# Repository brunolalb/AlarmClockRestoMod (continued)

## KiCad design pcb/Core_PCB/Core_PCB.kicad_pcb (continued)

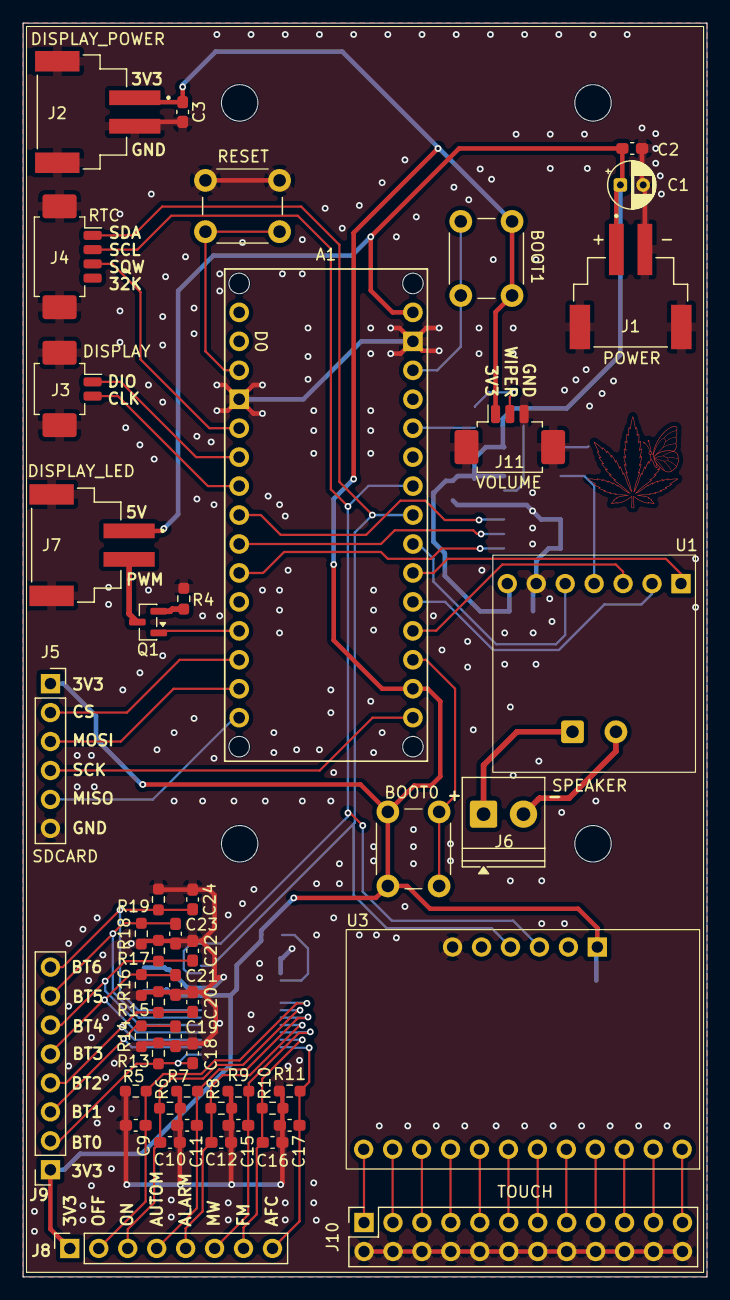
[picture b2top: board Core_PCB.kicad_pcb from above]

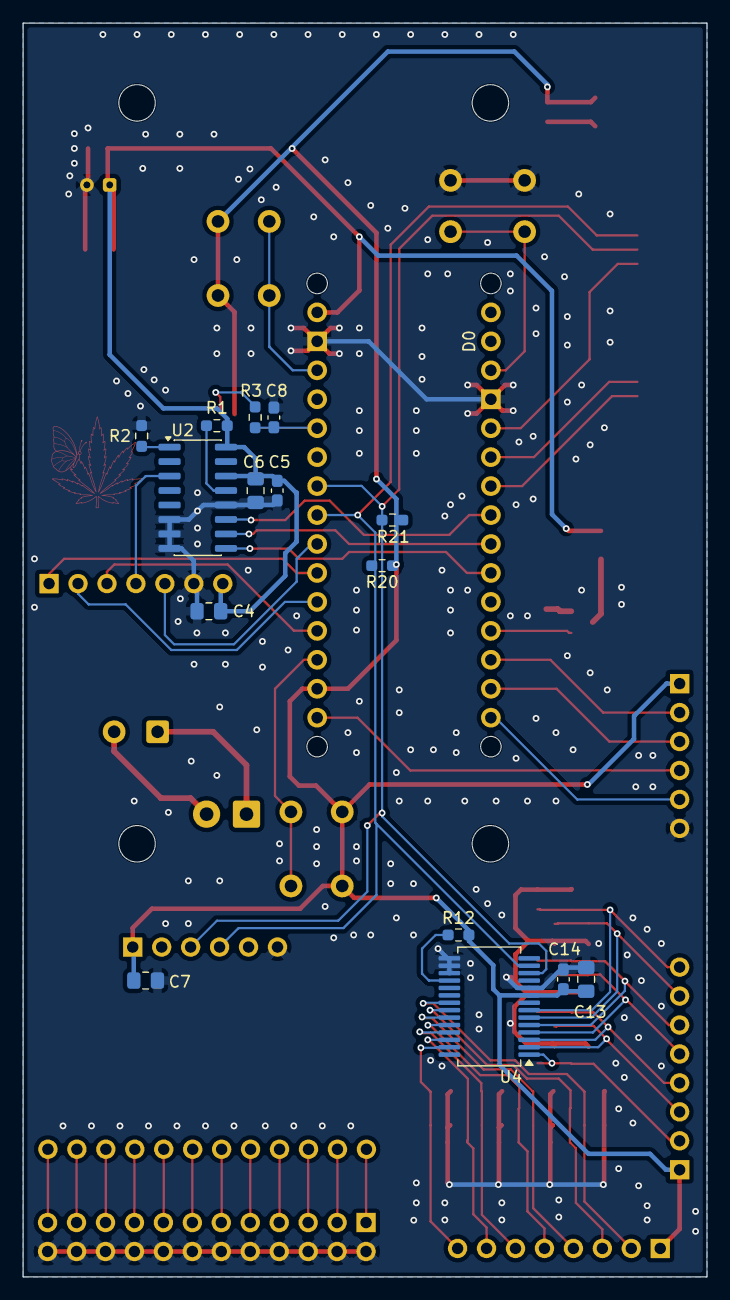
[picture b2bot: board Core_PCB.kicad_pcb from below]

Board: 2 copper layers, 60.0 x 110.0 mm, 70 parts (15 on the bottom side), 59 nets.

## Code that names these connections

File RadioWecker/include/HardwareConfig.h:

#pragma once

#include <Arduino.h>

/* Arduino Nano S3
                 ___
D13 - GPIO48 ---|   |--- D12 - GPIO47
3V3          ---|   |--- D11 - GPIO38
B0 - GPIO46  ---|   |--- D10 - GPIO21
A0 - GPIO1   ---|   |--- D9 - GPIO18
A1 - GPIO2   ---|   |--- D8 - GPIO17
A2 - GPIO3   ---|   |--- D7 - GPIO10
A3 - GPIO4   ---|   |--- D6 - GPIO9
A4 - GPIO11  ---|   |--- D5 - GPIO8
A5 - GPIO12  ---|   |--- D4 - GPIO7
A6 - GPIO13  ---|   |--- D3 - GPIO6
A7 - GPIO14  ---|   |--- D2 - GPIO5
VBUS         ---|   |--- GND
B1 - GPIO0   ---|   |--- RST
GND          ---|   |--- D0 - GPIO44
VIN          ---|___|--- D1 - GPIO43

*/

// on board LED
static constexpr uint8_t ONBOARD_LED_PIN = LED_RED;//46;

// shared I2C
static constexpr uint8_t I2C_SDA_PIN = A4;
static constexpr uint8_t I2C_SCL_PIN = A5;
static constexpr uint32_t I2C_FREQ_HZ = 100000;

// Display - TM1637
static constexpr uint8_t DISPLAY_CLK_PIN = D4;
static constexpr uint8_t DISPLAY_DIO_PIN = D3;

// todo: the TM1637 can only read one button at a time - move them to the MCP
static constexpr uint8_t DISPLAY_BUTTON_SLOW_GRID = 1;
static constexpr uint8_t DISPLAY_BUTTON_SLOW_KEY = 1;
static constexpr uint8_t DISPLAY_BUTTON_FAST_GRID = 1;
static constexpr uint8_t DISPLAY_BUTTON_FAST_KEY = 2;
static constexpr uint8_t DISPLAY_BUTTON_SLEEP_TOP_GRID = 2;
static constexpr uint8_t DISPLAY_BUTTON_SLEEP_TOP_KEY = 2;
static constexpr uint8_t DISPLAY_BUTTON_SIGNAL_GRID = 3;
static constexpr uint8_t DISPLAY_BUTTON_SIGNAL_KEY = 1;
static constexpr uint8_t DISPLAY_BUTTON_TIME_GRID = 3;
static constexpr uint8_t DISPLAY_BUTTON_TIME_KEY = 2;
static constexpr uint8_t DISPLAY_BUTTON_SLEEP_FRONT_GRID = 4;
static constexpr uint8_t DISPLAY_BUTTON_SLEEP_FRONT_KEY = 1;
static constexpr uint8_t DISPLAY_BUTTON_ILLUM_GRID = 4;
static constexpr uint8_t DISPLAY_BUTTON_ILLUM_KEY = 2;

static constexpr uint8_t DISPLAY_BUTTON_SLOW_CHANNEL = 99; //last one to check
static constexpr uint8_t DISPLAY_BUTTON_FAST_CHANNEL = 0;
static constexpr uint8_t DISPLAY_BUTTON_SLEEP_TOP_CHANNEL = 1;
static constexpr uint8_t DISPLAY_BUTTON_SIGNAL_CHANNEL = 10;
static constexpr uint8_t DISPLAY_BUTTON_TIME_CHANNEL = 2;
static constexpr uint8_t DISPLAY_BUTTON_SLEEP_FRONT_CHANNEL = 13;
static constexpr uint8_t DISPLAY_BUTTON_ILLUM_CHANNEL = 5;

// SD Card
static constexpr uint8_t SD_SPI_CS_PIN = D10;
static constexpr uint8_t SD_SPI_SCK_PIN = D13;
static constexpr uint8_t SD_SPI_MISO_PIN = D12;
static constexpr uint8_t SD_SPI_MOSI_PIN = D11;
static constexpr uint32_t SD_SPI_FREQUENCY_HZ = 10000000;

// RTC
static constexpr uint8_t RTC_I2C_SDA_PIN = I2C_SDA_PIN;
static constexpr uint8_t RTC_I2C_SCL_PIN = I2C_SCL_PIN;
static constexpr uint32_t RTC_I2C_FREQUENCY_HZ = I2C_FREQ_HZ;
static constexpr uint8_t RTC_SQW_PIN = D2;

// Audio - I2S - MAX9357A
static constexpr uint8_t I2S_LRCLK_PIN = 3; //A2;
static constexpr uint8_t I2S_BCLK_PIN = 2; //A1;
static constexpr uint8_t I2S_DATA_PIN = 1; //A0;
static constexpr uint8_t AUDIO_SD = A3;
static constexpr uint8_t AUDIO_GAIN_MUX_S1 = D5; // gain is controlled by HEF4051BT
static constexpr uint8_t AUDIO_GAIN_MUX_S2 = D6;
static constexpr uint8_t AUDIO_GAIN_MUX_S3 = D7;
static constexpr uint8_t AUDIO_VOLUME_POT = A7; // volume potentiometer is 100k
// Audio control
#define AUDIO_SHUTDOWN_MODE_OFF()  do { pinMode(AUDIO_SD, OUTPUT); digitalWrite(AUDIO_SD, LOW); } while (0)
#define AUDIO_SHUTDOWN_MODE_ON()   pinMode(AUDIO_SD, OPEN_DRAIN)
static constexpr uint8_t AUDIO_GAIN_3DB = 0b000;
static constexpr uint8_t AUDIO_GAIN_6DB = 0b100;
static constexpr uint8_t AUDIO_GAIN_9DB = 0b010;
static constexpr uint8_t AUDIO_GAIN_12DB = 0b110;
static constexpr uint8_t AUDIO_GAIN_15DB = 0b001;

// Light
static constexpr uint8_t LIGHT_PWM_PIN = D9;
static constexpr uint16_t LIGHT_PWM_FREQUENCY = 10000; // Hz

// Radio Dial - MPR121
static constexpr uint8_t RADIO_DIAL_I2C_SDA_PIN = I2C_SDA_PIN;
static constexpr uint8_t RADIO_DIAL_I2C_SCL_PIN = I2C_SCL_PIN;
static constexpr uint32_t RADIO_DIAL_I2C_FREQUENCY_HZ = I2C_FREQ_HZ;

// Radio Buttons - MCP23017
static constexpr uint8_t RADIO_BUTTONS_I2C_SDA_PIN = I2C_SDA_PIN;
static constexpr uint8_t RADIO_BUTTONS_I2C_SCL_PIN = I2C_SCL_PIN;
static constexpr uint32_t RADIO_BUTTONS_I2C_FREQUENCY_HZ = I2C_FREQ_HZ;
static constexpr uint8_t RADIO_BUTTONS_I2C_ADDRESS = 0x20;

static constexpr uint8_t RADIO_BUTTON_OFF_CHANNEL = 0; //GPA0
static constexpr uint8_t RADIO_BUTTON_ON_CHANNEL = 1; //GPA1
static constexpr uint8_t RADIO_BUTTON_AUTOM_CHANNEL = 2; //GPA2
static constexpr uint8_t RADIO_BUTTON_ALARM_CHANNEL = 3; //GPA3
static constexpr uint8_t RADIO_BUTTON_MW_CHANNEL = 4; //GPA4
static constexpr uint8_t RADIO_BUTTON_FM_CHANNEL = 5; //GPA5
static constexpr uint8_t RADIO_BUTTON_AFC_CHANNEL = 6; //GPA6

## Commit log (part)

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2026-05-12 Initial plan
2026-05-12 feat: add alarm clock control core and web ui
    Agent-Logs-Url: https://github.com/brunolalb/AlarmClockRestoMod/sessions/4cf85042-19a5-4d14-a2ee-58c3aa3bf729
2026-05-12 docs: make build and run commands portable
    Agent-Logs-Url: https://github.com/brunolalb/AlarmClockRestoMod/sessions/4cf85042-19a5-4d14-a2ee-58c3aa3bf729
2026-05-12 refactor: address review feedback in control server
    Agent-Logs-Url: https://github.com/brunolalb/AlarmClockRestoMod/sessions/4cf85042-19a5-4d14-a2ee-58c3aa3bf729
2026-05-12 style: fix final main formatting issue
    Agent-Logs-Url: https://github.com/brunolalb/AlarmClockRestoMod/sessions/4cf85042-19a5-4d14-a2ee-58c3aa3bf729
2026-05-12 refactor: replace remaining control-flow magic numbers
    Agent-Logs-Url: https://github.com/brunolalb/AlarmClockRestoMod/sessions/4cf85042-19a5-4d14-a2ee-58c3aa3bf729
2026-05-13 project setup with pioarduino, simple program to test tm1637 4 digit 7seg display, vibe coded on board led controller, base files for wokwi simulation
2026-05-13 added a rtc clock and microsd card to diagram, moved the display to software SPI, vibe coded a simple selftest for the sd card
2026-05-13 added a driver for the RTC, removed the counter, show colon if time is shown
2026-05-13 added the square wave pin from the rtc, so we dont have to use the i2c all the time
2026-05-13 added wifi connection with credentials saved in the internal memory, ntp synchronization
2026-05-13 vibecoding is getting out of hand...added a webserver with a page to configure alarms
2026-05-17 old wifimanager wasnt working great, moving on to tzapu (more well known)
2026-05-17 moved the sd card to its own library
2026-05-17 clock controller got its own library as well, it's responsible for keeping time and synchronizing with the RTC
2026-05-17 moved the display operations to its own library
2026-05-17 moved hardware definitions to its own header file
2026-05-21 moved the alarm controller to its own library and added a serial controller for simple debug commands
2026-05-21 added an index page, made everything dark mode, figured out how to send stuff to the littlefs
2026-05-21 webserver to its own lib
2026-05-21 added explicit hardware config to the sd card spi and rtc i2c
2026-05-21 added ntp synchronization to the clock, display shows hh:mm
2026-05-21 onboard led is shared with SCK pin, so moved it to the RGB led
2026-05-21 more useful info about the sd card
2026-05-21 single serial prints instead of too many
2026-05-21 general config page for timezone, time offset, display brightness
2026-05-21 general config moved to its own lib
2026-05-21 save the config on the sd card as well, sd card has priority
2026-05-21 save the alarms config on the sd card as well, sd card has priority
2026-05-21 added a status webpage
2026-05-21 added a FTP server to access the SD Card. user can change the username/password on the general configurations (password saved encrypted with mac)
2026-05-21 time wasnt showing properly when hour starts with 0
2026-05-21 clear the screen during initialization
2026-05-21 added back to home button to alarm, made all the same
2026-05-21 standardized style and added a shared stylesheet in its own file, so all pages look similar
2026-05-23 got a display that doesnt have the colon, but the rather the dots
2026-05-23 added a sound controller for the MAX98357A (pins have to be gpio, otherwise it doesnt work) and a webpage with simple controls and an upload files page.
2026-06-03 better sound player page, better controls, removed the radio (will add to its own page), more complete track list explorer
2026-06-05 replaced the RTC lib with adafruit's (also has the DateTime class, which is nicer to work with). update the RTC Chip once NTP is synced
2026-06-05 wifi connection non blocking, so the clock can start faster
2026-06-05 all accesses to the SD Card go through the SD Controller
2026-06-05 replaced the many handle* commands in the sound controller with a single function to concentrate all webserver commands
2026-06-05 moved the music file list to the sd controller instead of the sound controller (can be reused later on the upload/file explorer page)
2026-06-05 updated the api on the html files
2026-06-05 moved sd card handling in the webserver controller to the sd controller
2026-06-16 style: moved things around
2026-06-17 initial schematics. still missing interfaces connections
2026-06-17 unnecessary file
2026-06-17 SCH - buttons: added footprints, name is under Name instead of Reference and Reference follows normal "J?"
2026-06-17 SCH - display: name under Name
2026-06-17 SCH - rtc: adjusted footprints and direction of 32K label
2026-06-17 SCH - interface: added connectors (JST connectors) and labels
2026-06-17 SCH - top level: connected everything
2026-06-17 added project symbol and footprint libs
2026-06-18 SCH - buttons: added footprints to switches (will probably change, need a lower profile)
2026-06-18 SCH - interface: name under Name and reference follows J?
2026-06-18 PCB: positioning of critical parts and board shape according to original. initial positioning of all components
2026-06-18 PCB: initial layout idea
2026-06-18 SCH - buttons, display and interface: TM1637 can read the buttons (saves many resistors, caps and connectors)
2026-06-18 SCH - top level: reflect new button reading strategy
2026-06-18 PCB: updated with new button reading strategy (still missing VCC and GND routing)
2026-06-19 LIB - display: refined footprint (removed unnecessary info)
2026-06-19 LIB - RTC: better alignment of 3D body, removed unnecessary info
2026-06-19 SCH - buttons: added a table with which button is connected to where on the TM1637
2026-06-19 PCB: refined layout, added GND planes, connected VCC
2026-06-19 LIB: added SMD mounting pad
2026-06-19 SCH and PCB: added the Mounting Pads (a few chosen ones)
2026-06-19 SCH - interface: replaced symbols from connectors with mounting pads to contain the mounting pads (and connected them to GND)
2026-06-19 SCH and PCB: reannotated everything
2026-06-30 adjusted connectors footprints, added footprint to input polarized capacitor, rtc and display polarized capacitors converted to non polarized
